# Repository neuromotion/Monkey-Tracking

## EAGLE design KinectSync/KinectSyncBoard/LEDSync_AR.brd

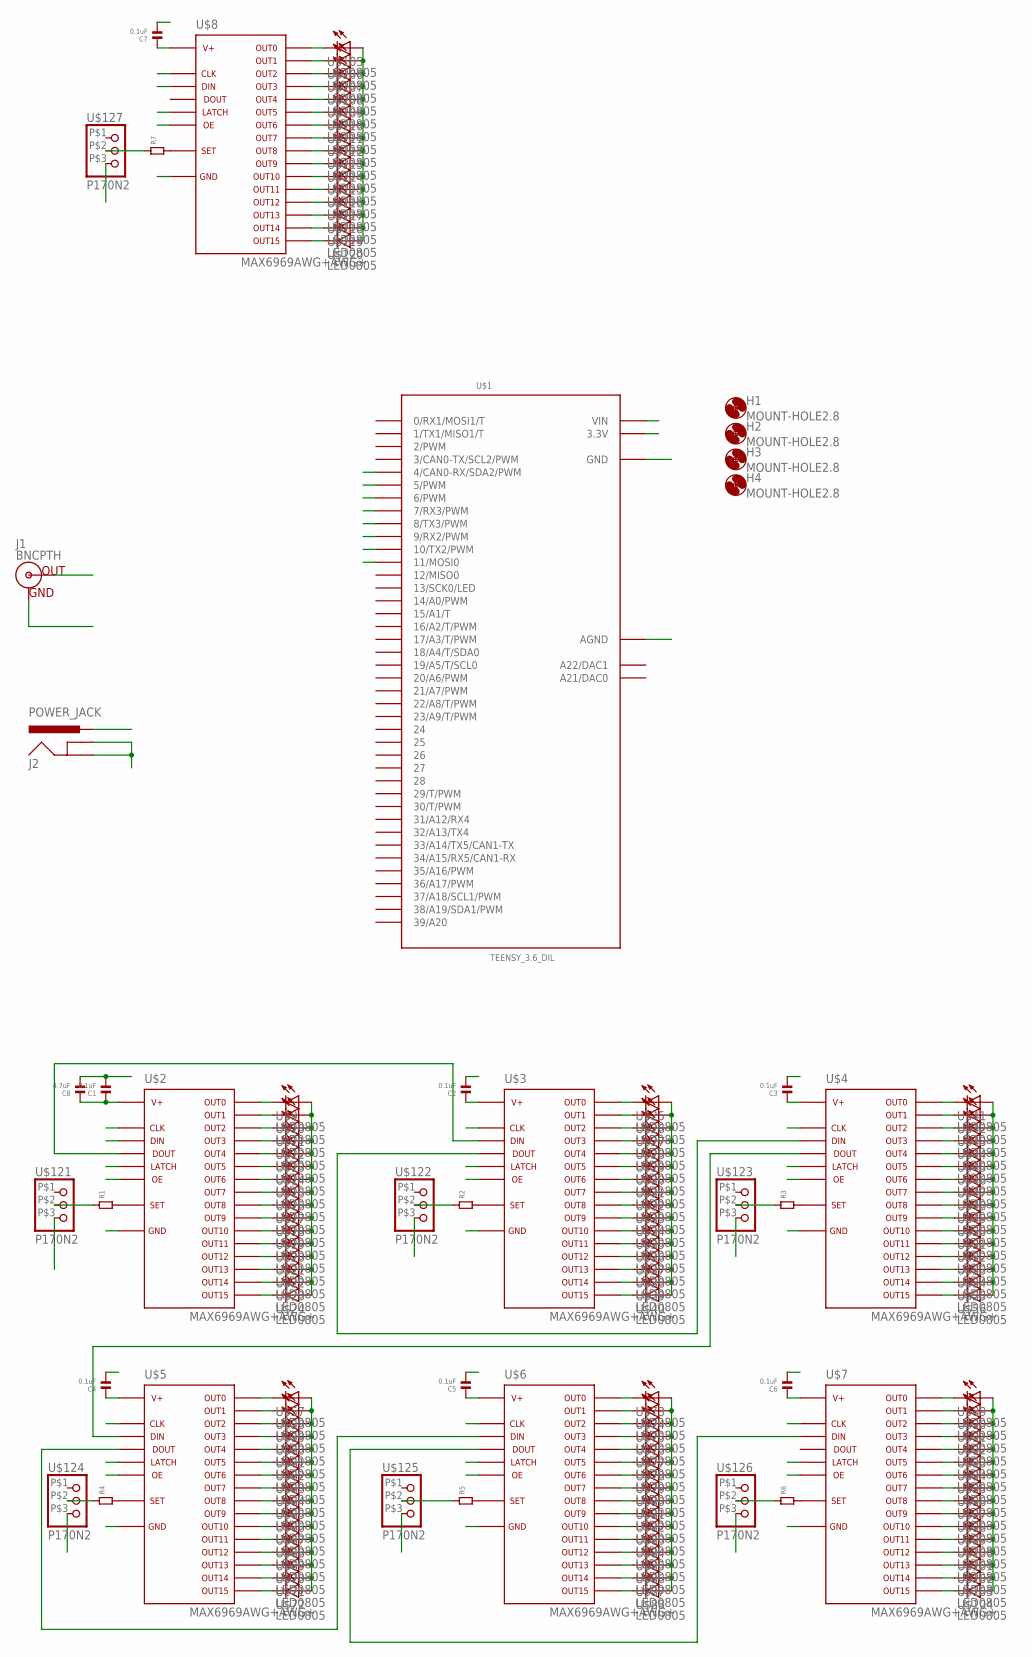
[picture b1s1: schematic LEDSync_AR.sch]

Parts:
C1, C2, C3, C4, C5, C6, C7: 0.1uF; 0805
C8: 4.7uF; 0805
H1, H2, H3, H4: MOUNT-HOLE2.8; 2,8
J1: BNCPTH; BNC
J2: POWER_JACK; POWER_JACK_PTH
R1, R2, R3, R4, R5, R6, R7: RESISTOR.0805; 0805
U$1: TEENSY_3.6_DIL
U$2, U$3, U$4, U$5, U$6, U$7, U$8: MAX6969AWG+AWG+; SO24L
U$9, U$10, U$11, U$12, U$13, U$14, U$15, U$16, U$17, U$18, U$19, U$20, U$21, U$22, U$23, U$24, U$25, U$26, U$27, U$28, U$29, U$30, U$31, U$32, U$33, U$34, U$35, U$36, U$37, U$38, U$39, U$40, U$41, U$42, U$43, U$44, U$45, U$46, U$47, U$48, U$49, U$50, U$51, U$52, U$53, U$54, U$55, U$56, U$57, U$58, U$59, U$60, U$61, U$62, U$63, U$64, U$65, U$66, U$67, U$68, U$69, U$70, U$71, U$72, U$73, U$74, U$75, U$76, U$77, U$78, U$79, U$80, U$81, U$82, U$83, U$84, U$85, U$86, U$87, U$88, U$89, U$90, U$91, U$92, U$93, U$94, U$95, U$96, U$97, U$98, U$99, U$100, U$101, U$102, U$103, U$104, U$105, U$106, U$107, U$108, U$109, U$110, U$111, U$112, U$113, U$114, U$115, U$116, U$117, U$118, U$119, U$120: LED0805; 0805
U$121, U$122, U$123, U$124, U$125, U$126, U$127: P170N2

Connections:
3V3: U$1.3.3V, U$1.3.3V3 (3.3V)
GND: C1.2, C2.2, C3.2, C4.2, C5.2, C6.2, C7.2, C8.2, J1.GND, J2.GND, J2.GNDBREAK, U$1.AGND, U$1.GND, U$1.GND1 (GND), U$2.1, U$3.1, U$4.1, U$5.1, U$6.1, U$7.1, U$8.1, U$121.P$3 (3), U$122.P$3 (3), U$123.P$3 (3), U$124.P$3 (3), U$125.P$3 (3), U$126.P$3 (3), U$127.P$3 (3)
G_CLK: U$1.5 (5/PWM), U$2.3, U$3.3, U$4.3, U$5.3, U$6.3, U$7.3
G_D: U$1.4 (4/CAN0-RX/SDA2/PWM), U$2.2
G_LE: J1.S (OUT), U$1.6 (6/PWM), U$2.4, U$3.4, U$4.4, U$5.4, U$6.4, U$7.4
G_OE: U$1.7 (7/RX3/PWM), U$2.21, U$3.21, U$4.21, U$5.21, U$6.21, U$7.21
unnamed: U$2.5, U$9.2 (C)
unnamed: U$2.6, U$10.2 (C)
unnamed: U$2.7, U$11.2 (C)
unnamed: U$2.8, U$12.2 (C)
unnamed: U$2.9, U$13.2 (C)
unnamed: U$2.10, U$14.2 (C)
unnamed: U$2.11, U$15.2 (C)
unnamed: U$2.12, U$16.2 (C)
unnamed: U$2.13, U$17.2 (C)
unnamed: U$2.14, U$18.2 (C)
unnamed: U$2.15, U$19.2 (C)
unnamed: U$2.16, U$20.2 (C)
unnamed: U$2.17, U$21.2 (C)
unnamed: U$2.18, U$22.2 (C)
unnamed: U$2.19, U$23.2 (C)
unnamed: U$2.20, U$24.2 (C)
unnamed: U$3.5, U$25.2 (C)
unnamed: U$3.6, U$26.2 (C)
unnamed: U$3.7, U$27.2 (C)
unnamed: U$3.8, U$28.2 (C)
unnamed: U$3.9, U$29.2 (C)
unnamed: U$3.10, U$30.2 (C)
unnamed: U$3.11, U$31.2 (C)
unnamed: U$3.12, U$32.2 (C)
unnamed: U$3.13, U$33.2 (C)
unnamed: U$3.14, U$34.2 (C)
unnamed: U$3.15, U$35.2 (C)
unnamed: U$3.16, U$36.2 (C)
unnamed: U$3.17, U$37.2 (C)
unnamed: U$3.18, U$38.2 (C)
unnamed: U$3.19, U$39.2 (C)
unnamed: U$3.20, U$40.2 (C)
unnamed: U$4.5, U$41.2 (C)
unnamed: U$4.6, U$42.2 (C)
unnamed: U$4.7, U$43.2 (C)
unnamed: U$4.8, U$44.2 (C)
unnamed: U$4.9, U$45.2 (C)
unnamed: U$4.10, U$46.2 (C)
unnamed: U$4.11, U$47.2 (C)
unnamed: U$4.12, U$48.2 (C)
unnamed: U$4.13, U$49.2 (C)
unnamed: U$4.14, U$50.2 (C)
unnamed: U$4.15, U$51.2 (C)
unnamed: U$4.16, U$52.2 (C)
unnamed: U$4.17, U$53.2 (C)
unnamed: U$4.18, U$54.2 (C)
unnamed: U$4.19, U$55.2 (C)
unnamed: U$4.20, U$56.2 (C)
unnamed: U$5.5, U$57.2 (C)
unnamed: U$5.6, U$58.2 (C)
unnamed: U$5.7, U$59.2 (C)
unnamed: U$5.8, U$60.2 (C)
unnamed: U$5.9, U$61.2 (C)
unnamed: U$5.10, U$62.2 (C)
unnamed: U$5.11, U$63.2 (C)
unnamed: U$5.12, U$64.2 (C)
unnamed: U$5.13, U$65.2 (C)
unnamed: U$5.14, U$66.2 (C)
unnamed: U$5.15, U$67.2 (C)
unnamed: U$5.16, U$68.2 (C)
unnamed: U$5.17, U$69.2 (C)
unnamed: U$5.18, U$70.2 (C)
unnamed: U$5.19, U$71.2 (C)
unnamed: U$5.20, U$72.2 (C)
unnamed: U$6.5, U$73.2 (C)
unnamed: U$6.6, U$74.2 (C)
unnamed: U$6.7, U$75.2 (C)
unnamed: U$6.8, U$76.2 (C)
unnamed: U$6.9, U$77.2 (C)
unnamed: U$6.10, U$78.2 (C)
unnamed: U$6.11, U$79.2 (C)
unnamed: U$6.12, U$80.2 (C)
unnamed: U$6.13, U$81.2 (C)
unnamed: U$6.14, U$82.2 (C)
unnamed: U$6.15, U$83.2 (C)
unnamed: U$6.16, U$84.2 (C)
unnamed: U$6.17, U$85.2 (C)
unnamed: U$6.18, U$86.2 (C)
unnamed: U$6.19, U$87.2 (C)
unnamed: U$6.20, U$88.2 (C)
unnamed: U$7.5, U$89.2 (C)
unnamed: U$7.6, U$90.2 (C)
unnamed: U$7.7, U$91.2 (C)
unnamed: U$7.8, U$92.2 (C)
unnamed: U$7.9, U$93.2 (C)
unnamed: U$7.10, U$94.2 (C)
unnamed: U$7.11, U$95.2 (C)
unnamed: U$7.12, U$96.2 (C)
unnamed: U$7.13, U$97.2 (C)
unnamed: U$7.14, U$98.2 (C)
unnamed: U$7.16, U$100.2 (C)
unnamed: U$7.17, U$101.2 (C)
unnamed: U$7.18, U$102.2 (C)
unnamed: U$7.19, U$103.2 (C)
unnamed: U$7.20, U$104.2 (C)
unnamed: U$8.5, U$105.2 (C)
unnamed: U$8.6, U$106.2 (C)
unnamed: U$8.7, U$107.2 (C)
unnamed: U$8.8, U$108.2 (C)
unnamed: U$8.10, U$110.2 (C)
unnamed: U$8.11, U$111.2 (C)
unnamed: U$8.12, U$112.2 (C)
unnamed: U$8.13, U$113.2 (C)
unnamed: U$8.14, U$114.2 (C)
unnamed: U$8.15, U$115.2 (C)
unnamed: U$8.16, U$116.2 (C)
unnamed: U$8.17, U$117.2 (C)
unnamed: U$8.18, U$118.2 (C)
unnamed: U$8.19, U$119.2 (C)
unnamed: U$8.20, U$120.2 (C)
unnamed: U$8.9, U$109.2 (C)
unnamed: U$7.15, U$99.2 (C)
unnamed: R1.2, U$2.23
unnamed: R2.2, U$3.23
unnamed: R3.2, U$4.23
unnamed: R4.2, U$5.23
unnamed: R5.2, U$6.23
unnamed: R6.2, U$7.23
unnamed: R7.2, U$8.23
unnamed: R7.1, U$127.P$2 (2)
unnamed: U$2.22, U$3.2
unnamed: R1.1, U$121.P$2 (2)
unnamed: R2.1, U$122.P$2 (2)
unnamed: R3.1, U$123.P$2 (2)
unnamed: R6.1, U$126.P$2 (2)
unnamed: R5.1, U$125.P$2 (2)
unnamed: R4.1, U$124.P$2 (2)
unnamed: U$3.22, U$4.2
unnamed: U$4.22, U$5.2
unnamed: U$5.22, U$6.2
unnamed: U$6.22, U$7.2
T_CLK: U$1.9 (9/RX2/PWM), U$8.3
T_D: U$1.8 (8/TX3/PWM), U$8.2
T_LE: U$1.10 (10/TX2/PWM), U$8.4
T_OE: U$1.11 (11/MOSI0), U$8.21
VIN: C1.1, C2.1, C3.1, C4.1, C5.1, C6.1, C7.1, C8.1, J2.PWR, U$1.VIN, U$2.24, U$3.24, U$4.24, U$5.24, U$6.24, U$7.24, U$8.24, U$9.1 (A), U$10.1 (A), U$11.1 (A), U$12.1 (A), U$13.1 (A), U$14.1 (A), U$15.1 (A), U$16.1 (A), U$17.1 (A), U$18.1 (A), U$19.1 (A), U$20.1 (A), U$21.1 (A), U$22.1 (A), U$23.1 (A), U$24.1 (A), U$25.1 (A), U$26.1 (A), U$27.1 (A), U$28.1 (A), U$29.1 (A), U$30.1 (A), U$31.1 (A), U$32.1 (A), U$33.1 (A), U$34.1 (A), U$35.1 (A), U$36.1 (A), U$37.1 (A), U$38.1 (A), U$39.1 (A), U$40.1 (A), U$41.1 (A), U$42.1 (A), U$43.1 (A), U$44.1 (A), U$45.1 (A), U$46.1 (A), U$47.1 (A), U$48.1 (A), U$49.1 (A), U$50.1 (A), U$51.1 (A), U$52.1 (A), U$53.1 (A), U$54.1 (A), U$55.1 (A), U$56.1 (A), U$57.1 (A), U$58.1 (A), U$59.1 (A), U$60.1 (A), U$61.1 (A), U$62.1 (A), U$63.1 (A), U$64.1 (A), U$65.1 (A), U$66.1 (A), U$67.1 (A), U$68.1 (A), U$69.1 (A), U$70.1 (A), U$71.1 (A), U$72.1 (A), U$73.1 (A), U$74.1 (A), U$75.1 (A), U$76.1 (A), U$77.1 (A), U$78.1 (A), U$79.1 (A), U$80.1 (A), U$81.1 (A), U$82.1 (A), U$83.1 (A), U$84.1 (A), U$85.1 (A), U$86.1 (A), U$87.1 (A), U$88.1 (A), U$89.1 (A), U$90.1 (A), U$91.1 (A), U$92.1 (A), U$93.1 (A), U$94.1 (A), U$95.1 (A), U$96.1 (A), U$97.1 (A), U$98.1 (A), U$99.1 (A), U$100.1 (A), U$101.1 (A), U$102.1 (A), U$103.1 (A), U$104.1 (A), U$105.1 (A), U$106.1 (A), U$107.1 (A), U$108.1 (A), U$109.1 (A), U$110.1 (A), U$111.1 (A), U$112.1 (A), U$113.1 (A), U$114.1 (A), U$115.1 (A), U$116.1 (A), U$117.1 (A), U$118.1 (A), U$119.1 (A), U$120.1 (A)

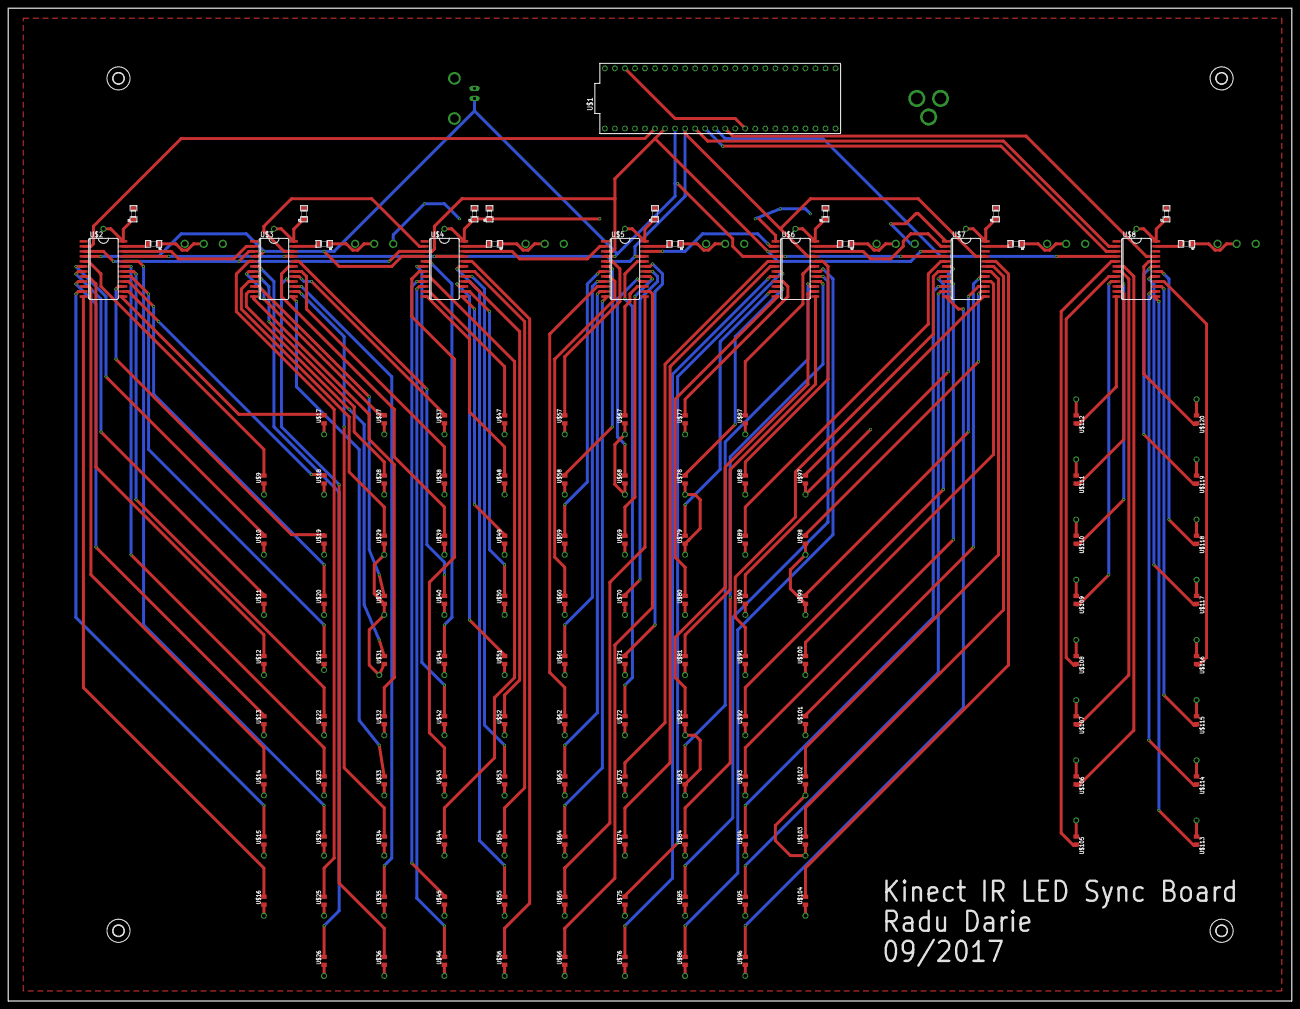
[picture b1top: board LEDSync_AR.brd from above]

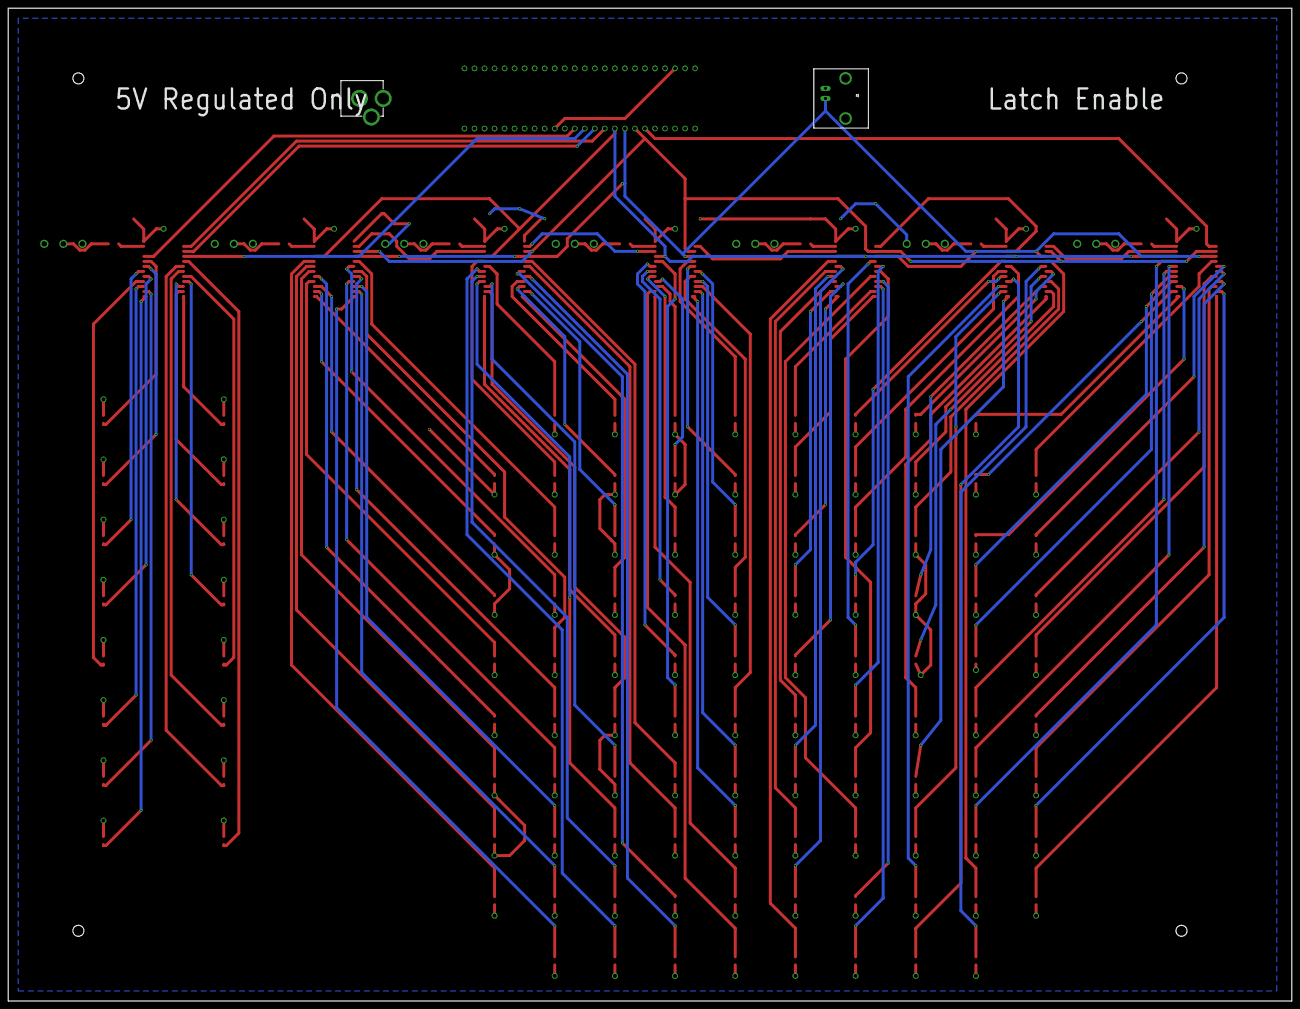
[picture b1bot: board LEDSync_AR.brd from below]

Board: 2 copper layers, 325.1 x 251.5 mm, 148 parts (2 on the bottom side), 142 nets.

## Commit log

2016-11-22 :octocat: Added .gitattributes & .gitignore files
2017-03-16 (slow) video player
2017-08-22 IR synch device
2017-09-21 board pin assignments
2017-10-04 small changes
2017-12-08 added LED synching code
2017-12-15 fixed a bug
2017-12-15 LED Sync Board layout
2018-03-15 fixed error that caused an extra empty frame every 97 frames
2018-03-15 actually fix the last problem
2018-10-11 big update

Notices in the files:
parts and their libraries:
SparkFun-Connectors: Licensing: Creative Commons ShareAlike 4.0 International - https://creativecommons.org/licenses/by-sa/4.0
